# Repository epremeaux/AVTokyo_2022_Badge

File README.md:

## AVTokyo 2022 event badge

### MQTT enabled, Hacker tools, Sensors and Games on ESP32
The AVTokyo 2022 event attendee badge was designed and produced by VPCAsia. Our vision was to provide a useful tool for the attendee not only at the event, but far into the future.

It is based on an 8MB ESP32 with 280x240 pixel TFT full color display (sourced from smart watches). Additionally, it includes a joystick (4 directions plus “press to select”), two game buttons (B and A), and two sensors (Temperature/Humidity and Accelerometer). Finally, the device is fully battery powered, relying on an 18650 style Li-ion battery with associated protections and USB charging.

The software runs a variety of open source Arduino libraries. In particular, we utilized [tcMenu](https://www.thecoderscorner.com/products/arduino-libraries/tc-menu/) and TFT_eSPI to provide all of our software UI, and Adafruit libraries to manage sensors and MQTT (Message Queue, Telemetry Transport).

While WiFi is connected and MQTT messaging is enabled, the badge will send Temperature, Humidity and Battery Voltage measurements to an MQTT server every 5 seconds (the interval is redefinable). Additionally, when you obtain a new best personal score on any game, the new score will be queued to be sent in the next MQTT post. While gaming, MQTT posting is temporarily disabled, in order to provide the best gaming experience.

Here is a video:

## Tour of the Board
Most of the badge components are self-explanatory, but I will attempt to highlight the main components and features. The circuitry between the joystick and screen is responsible for charging the battery (on the back). This is fed from the USB connector, and will charge the battery even when the badge is switched off. There are two LEDs, Standby and Charge. Once fully charged, the Charge LED will turn off and the Standby LED will light. These are rather bright! I started placing tape over my test units to dampend the brightness. ;)

Directly below the screen are the two sensors. On the right, we have an SHTC3 temperature and humidity sensor. On the left we have the KXTJ3-1057 accelerometer. Its not a particularly expensive device, so don't expect much. It's good enough for basic movement and orientation measurement. In the future, I hope to write some better drivers and filters for it to make the data more usable. At which point, I'll try to make a game using tilt/movement.

Above the power switch (bottom right) we have the battery protection circuits and voltage regulator which powers the board. The protection circuit is a very basic back to back mosfet configuration. The control IC *Should* cut power when the battery voltage gets below 3.2, but in my testing this turned out not to be the case. So, until I perform further tests, please dont trust this circuit to protect your battery from long term discharge. Remove the battery for storage.

Speaking of that power switch....   :(     Yes, now we know it's terrible. Attendee @mimura1133 found some alternate part numbers from Digikey if you have the skills to replace the switch. EG1215AA and CUS-12TB should fit. The part used on the badge is from G-Switch, MK-12C02-GXXX. We have yet to determine if this was a case of bad quality switches, or something in the reflow oven process made some of the switch plastics brittle. While this issue seemed considerable at the time of the event, we only had 42 total switch failures (of 400). The cracked resistor on the joystick was actually a higher failure rate.

Above the screen on the left we have the USB connector and associated ESP32 programming circuitry. This consists mainly of a USB to UART interface chip (CH340) and the Enable / Boot config buttons. Under normal circumstances using USB to program the badge, you should not need to bother with the buttons. If you get into a jam though, its nice to be able to manually trigger them. Additionally, the left button (enable) can be used as a reset button, so you dont have to toggle the power switch.
The USB connector can not only be used for programming but provides serial output from the ESP32 as well. There are some diagnostic messages as the badge goes through various tasks. The WiFi and Bluetooth scanners also output a lot of additional data here which cant possibly fit on the screen.

At the screen's top right corner we have a user LED and backlight control circuitry. The LED can be used for your own applications as well. We only use it to indicate the completion of the boot process (sort of a debugging tool for us).

Above the right side of the screen on the edge of the PCB we included some features for your own projects and future expansion. First, there is an I2C "Quiic" footprint. You will need to obtain and solder this yourself (was impossible at the time of production due to supply chain issues). This is a JST BM04B-SRSS connector or equivalent. 
To the right of the Quiic connector is a 5 pin header (2.54 mm pitch). This has ground, 3.3 volts, and three free GPIO from the ESP32. We are excited to see what you all come up with for these connections.

The back of the badge is dominated by the large 18650 lithium-ion battery holder at the bottom. Right in the middle is the ribbon cable for the screen. At top center we have the ESP32 module itself. This is an ESP32-Wroom-32 8MB part. Yes, it really IS 8MB. The firmware as flashed on the day of the event has a 4MB partition configuration. However, if you build fresh from this repository, it will build an 8Mb partition. All of our code now occupies only 20%! Lots of room left for more games, tools and custom apps. In the near future we will make some tutorials on how to add your project to the badge menu.

## Fixes to the production version
The PCB production and most of the component mounting was completed by JLCPCB. However, we still had some work to do. We glued the displays to the PCB and soldering the ribbon cable to the backside ourselves. Additionally, we mounted the battery case. However, you may notice some.. urr.. "Corrections" to some parts around the joystick. Unfortunately, I (Emery) made a mistake on the fill pattern, in which two pull-up resistors did not get connected to 3.3 Volts. So, we had to scrape away some of the solder mask and solder zero ohm jumpers to connect these resistors to the 3.3 volt fill. This added a LOT of additional work. The kicad files have been corrected. So if you attempt to produce the board yourself, don't worry.

We did experience a very unusual issue during production. Thankfully, I had created this a hardware test firmware before the final code was complete, so that we could test all functions before performing final firmware flashing. This test code included the Button Test (in the tools menu) as well as the Sensors page to confirm sensors were working.
The issue we found is that many (like, 1 of every 5 to 10) badges would indicate Left on the joystick, permanently. It took some time to identify the issue: The associated pull-up resistor (R8, on the left side of the joystick) was cracked. The crack is nearly impossible to see, even with a good magnifying lense. However, when we attempted to desolder it, it came off in two pieces! We were able to replace this resistor and managed to save 58 badges.

## About the Server
On our server side, we used a variety of services. It all starts by receiving the MQTT message in the MQTT server. From here, messages are written to a database using some custom Java.
From this database we then made web pages to output various statistics. In particular, we wanted to make a scoreboard for the two games included with the badge.

MQTT is simply a message bucket service. Many other services can subscribe to it. In fact, the code which writes to the database simply subscribes to the MQTT messages. Because this concept is so flexible, other services can easily subscribe at the same time.

Node-Red is a very user friendly GUI based data application builder. It was a simple matter to create a Node-Red flow to subscribe to badge topics using wild cards, allowing us to easily gather temperature measurements from ALL badges at once for example. This same flow outputs a web page with gauges, plots and text data. Node-Red performance is not very quick, but because it is only subscribing to topics (and another service handles database work), it has no impact on MQTT or our database.

### WiFi BugHunt
WE had one more game to play at the event: a WiFi BugHunt! These consisted of an ESP32 with battery pack hidden inside the nightclub (see AVTokyo_2022_Badge/Software/AVT_FindMe_Switcher/). Using the WiFi scanner tool in the badge (or your smartphone), players could seek out the three hidden WiFi access points. Once found, there was a QR code printed on the container of the WiFi AP. Scanning the code with your smartphone would bring you to a guest book web page, where you could sign that you found the AP and leave a comment. To make it more challenging, the APs occasionally dropped AP mode and joined local WiFi to send us an MQTT message containing the battery voltage, so we could monitor the devices in real time. It was quite entertaining to see all the script attacks people tried on our guestbook page ;)

## Getting the code up and running
The source code is "almost ready to run". You will need to install an editor such as Visual Studio Code. Within VSCode, add the PlatformIO extension. After opening the sourcecode folder, PlatformIO SHOULD download all the required extensions (mainly the Arduino framework and the ESP32 platform). All the required libraries are already included in the source code folder (.pio/libdeps/esp32dev/).
Depending on your initial VSCode and PlatformIO configuration, you MAY need to add "lorol/LittleFS_esp32@^1.0.6" to the platform.ini file, under the "lib_deps = " heading. If during compile you receive errors concerning LittleFS, either add it to the platform.ini file, or remove it (just add ; to the beginning of the line).

Additionally, you will need to create a "secrets.h" file like so:
```

//wifi
#define SECRET_SSID "your first AP"
#define SECRET_PASS "AP1 password"

#define SECRET_SSID2 "Second AP"
#define SECRET_PASS2 "AP2 password"

#define SECRET_SSID3 "third AP"
#define SECRET_PASS3 "AP3 password"

//mqtt
#define SECRET_SERVER "MQTT URL or IP" 

```

You can add as many WiFi access points as you want. Look at the MyWiFi.cpp file to add them to the array. The badge will first try to connect to whatever AP you have saved manually from the menu system. If that connection fails, it will then scan through the list given at the top of MyWiFi.cpp (the list is filled in from the secrets.h file). It will try to match any of these AP names to a scanned list available. If one matches, it will try to connect.

In addition to WiFi, you may want to point the badge to your own MQTT server. You may enter it manually in the menu, but you may prefer to hard code it. We have only defined the SECRET_SERVER keyword in the secrets.h file. This assumes an unsecured connection. So, you may want to modify MQTT_Sensors.cpp and secrets.h such that you can define a username and access key in secrets.h.

### UPDATE (22/11/24):

While experimenting with some badges, I found that SOME badges have 4MB ESP32 modules, and some have 8MB modules. Of course, we ORDERED 8MB modules. If you are attempting to compile and run this code and the following effects happen (after upload and reset), you likely have a 4MB module:

* red LED at the top right corner of the screen remains dimly light
* nothing displayed on screen
* when using the terminal, you see that the ESP is rapidly rebooting, with the following output: 
```
rst:0x3 (SW_RESET),boot:0x13 (SPI_FAST_FLASH_BOOT)
configsip: 0, SPIWP:0xee
clk_drv:0x00,q_drv:0x00,d_drv:0x00,cs0_drv:0x00,hd_drv:0x00,wp_drv:0x00
mode:DIO, clock div:2
load:0x3fff0030,len:1184
load:0x40078000,len:12776
load:0x40080400,len:3032
entry 0x400805e4
ets Jul 29 2019 12:21:46
```

PlatformIO is building an image set larger than the size of the flash storage area. However, it cannot by itself, verify the size. All the checksums are fine. You can confirm the size of your ESP's flash area yourself though. Look in the upload task terminal. When you hit the compile button (check mark on the bottom of VSCode window), one of hte first few lines will read:
HARDWARE: ESP32 240MHz, 320KB RAM, 4MB Flash
OR
HARDWARE: ESP32 240MHz, 320KB RAM, 8MB Flash

IF you were unlucky enough to get a 4MB module, we are so sorry.. but we cant control unscrupulous suppliers *(
What to do:
in the platformio.ini file, find the line which reads:

```
board_build.partitions = AVT_8MB_huge.csv
```

Change it to read:

```
board_build.partitions = huge_app.csv
```

This will use a standard partition table for a 4MB ESP32, where most of the space is devoted to a single app, plus bootloader. The base AVT code will occupy 51.5%, still leaving plenty of space for future enhancements.
By the way, this partition table is the one used in all of the badges on the day of the event. This is why I did not notice that we had a mix of 4MB and 8MB modules. So, I dont know yet what the statistics are on how many of you have each type.

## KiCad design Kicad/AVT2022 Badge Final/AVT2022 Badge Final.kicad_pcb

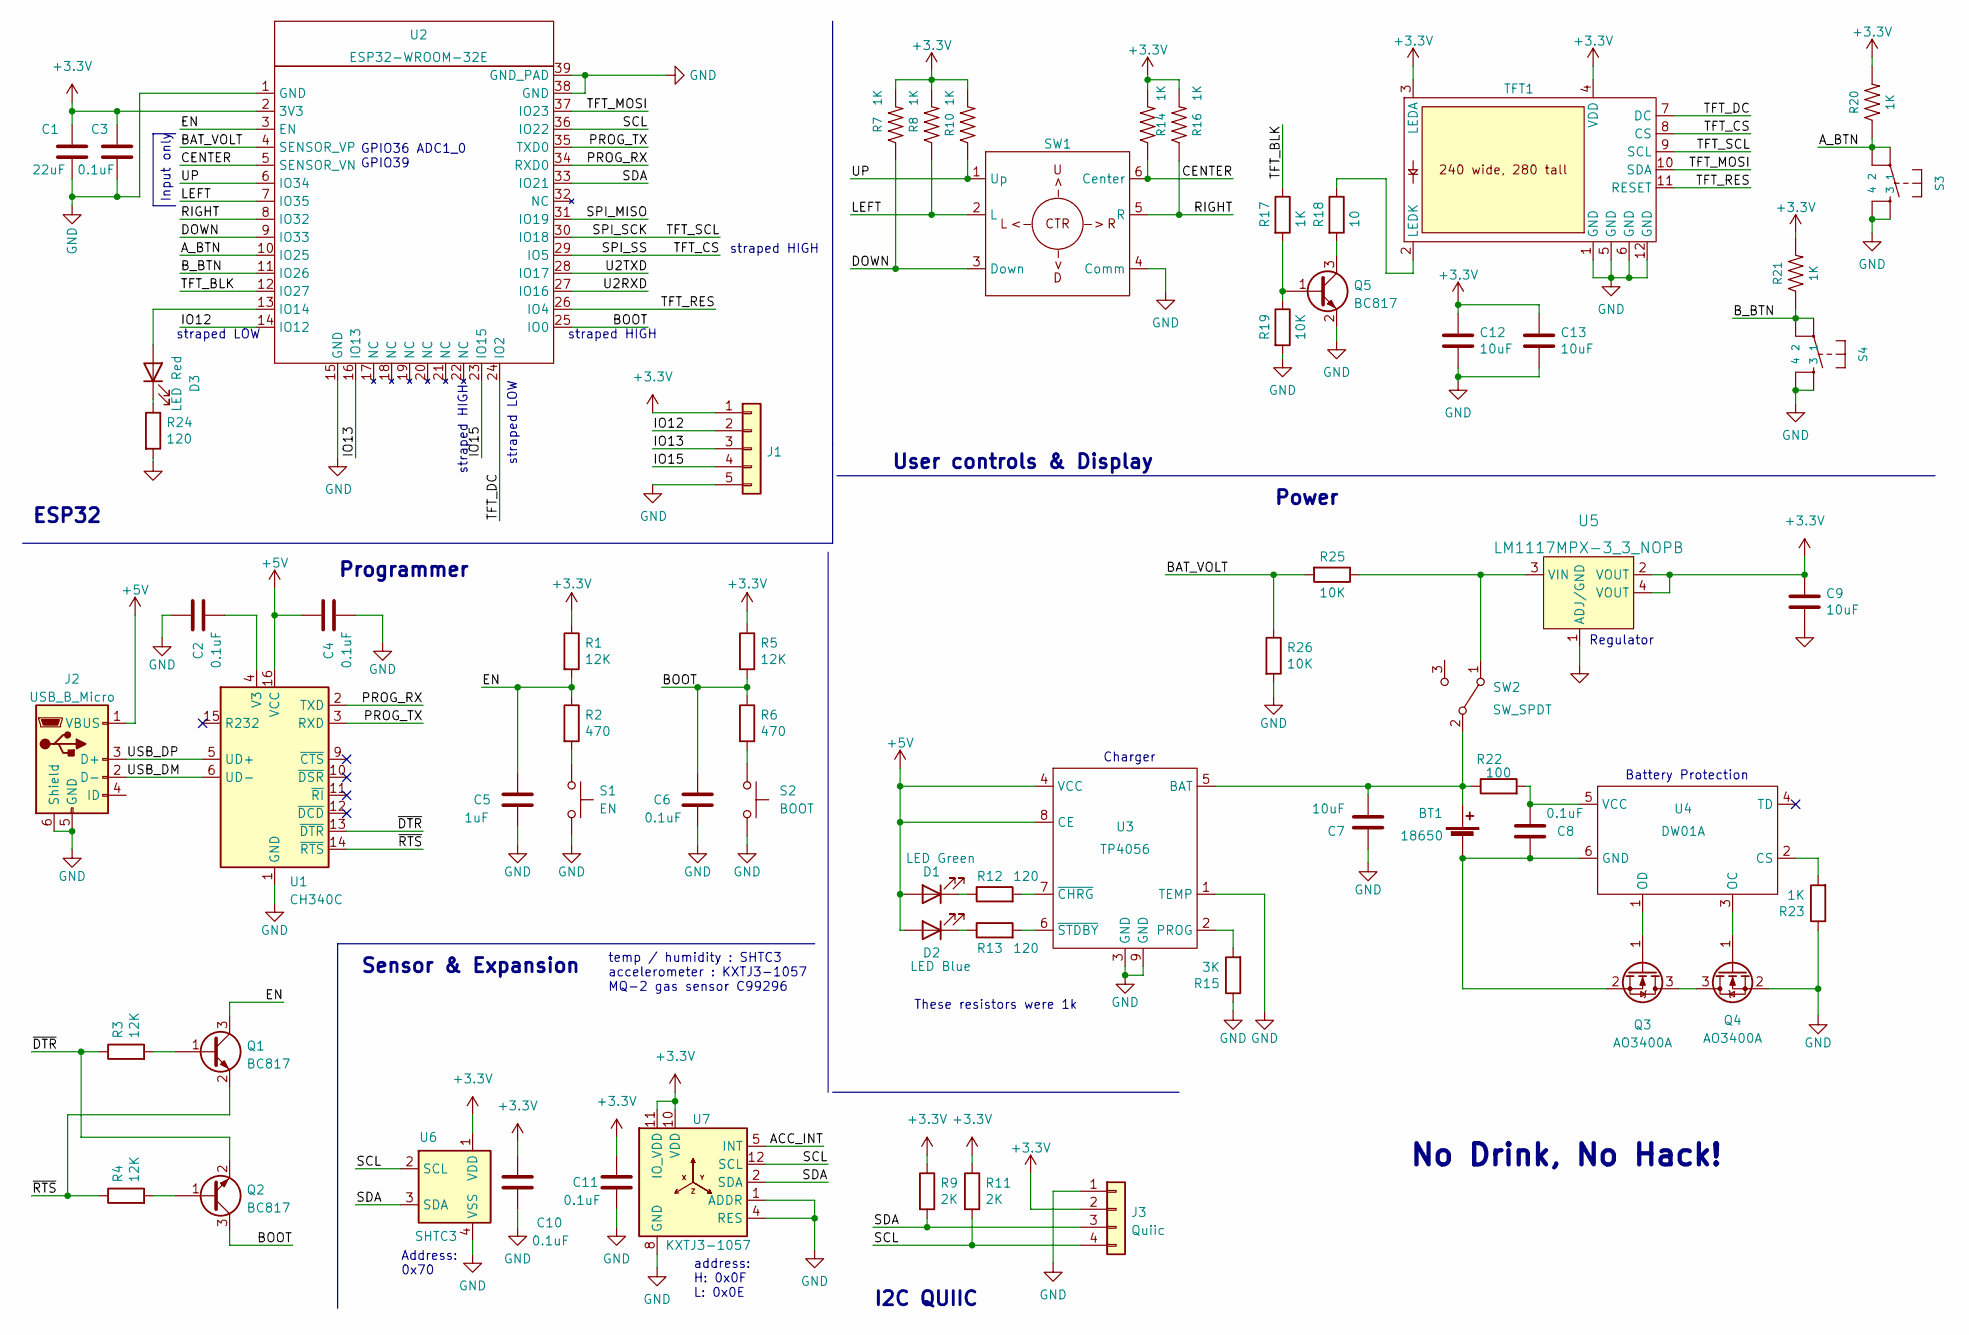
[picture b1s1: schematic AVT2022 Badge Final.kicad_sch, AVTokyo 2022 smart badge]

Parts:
BT1: 18650; BatteryHolder_Keystone_1042_1x18650; JLCPCB Status DO NOT POPULATE
C1: 22uF; C_0805_2012Metric_Pad1.18x1.45mm_HandSolder; JLCPCB# C89572
C2, C3, C4, C6, C8, C10, C11: 0.1uF; C_0805_2012Metric_Pad1.18x1.45mm_HandSolder; JLCPCB# C49678
C5: 1uF; C_0805_2012Metric_Pad1.18x1.45mm_HandSolder; JLCPCB# C28323
C7, C9, C12, C13: 10uF; C_0805_2012Metric_Pad1.18x1.45mm_HandSolder; JLCPCB# C15850
D1: LED Green; LED_0805_2012Metric; JLCPCB Status extended
D2: LED Blue; LED_0805_2012Metric; JLCPCB Status basic
D3: LED Red; LED_0805_2012Metric; JLCPCB Status basic
J1: Conn_01x05; PinHeader_1x05_P2.54mm_Vertical; JLC_Status DO NOT POPULATE
J2: USB_B_Micro; USB_Micro-AB_Molex_47590-0001; JLCPCB Status extended
J3: Quiic; JST_SH_BM04B-SRSS-TB_1x04-1MP_P1.00mm_Vertical; JLC_Status DO NOT POPULATE
Q1, Q2, Q5: BC817; SOT-23; JLCPCB Status extended
Q3, Q4: AO3400A; SOT-23; JLCPCB Status basic
R1, R3, R4, R5: 12K; R_0805_2012Metric_Pad1.20x1.40mm_HandSolder; JLCPCB# C17444
R2, R6: 470; R_0805_2012Metric_Pad1.20x1.40mm_HandSolder; JLCPCB# C17710
R7, R8, R10, R14, R16, R17, R20, R21, R23: 1K; R_0805_2012Metric_Pad1.20x1.40mm_HandSolder; JLCPCB# C17513
R9, R11: 2K; R_0805_2012Metric_Pad1.20x1.40mm_HandSolder; JLCPCB# C17604
R12, R13, R24: 120; R_0805_2012Metric_Pad1.20x1.40mm_HandSolder; JLCPCB# C17437
R15: 3K; R_0805_2012Metric_Pad1.20x1.40mm_HandSolder; JLCPCB# C17661
R18: 10; R_0805_2012Metric_Pad1.20x1.40mm_HandSolder; JLCPCB# C176204
R19, R25: 10K; R_0805_2012Metric_Pad1.20x1.40mm_HandSolder; JLCPCB# C17414
R22: 100; R_0805_2012Metric_Pad1.20x1.40mm_HandSolder; JLCPCB# C17408
R26: 10K; R_0805_2012Metric_Pad1.20x1.40mm_HandSolder; JLCPCB# C17621
S1: EN; SW_Push_1P1T_NO_CK_KMR2; JLCPCB Status extended
S2: BOOT; SW_Push_1P1T_NO_CK_KMR2; JLCPCB Status extended
S3, S4: MOMENTARY-SWITCH-SPST-2-SMD-5.2MM; Switch_Tactile_SMD_6x6mm; JLCPCB Status extended
SW1: navigation_switch_K1-1506SN-01; K1-1506SN-01; JLCPCB Status extended
SW2: SW_SPDT; MK-12C02-Gxxx SPDT SMD switch; JLCPCB Status extended
TFT1: TFT_240x280_raw_LH169I-IG01; TFT_240x280_raw_LH169I-IG01_BackSideMount; JLC_Status DO NOT POPULATE
U1: CH340C; SOIC-16_3.9x9.9mm_P1.27mm; JLCPCB Status extended
U2: ESP32-WROOM-32E; JLCPCB Status extended
U3: TP4056; TI_SO-PowerPAD-8; JLCPCB Status extemded
U4: DW01A; SOT-23-6; JLCPCB Status extemded
U5: LM1117MPX-3_3_NOPB; SOT-223; MPN LM1117MPX-3.3/NOPB; Digi-Key_PN LM1117MPX-3.3/NOPBCT-ND
U6: SHTC3; Sensirion_DFN-4-1EP_2x2mm_P1mm_EP0.7x1.6mm; JLCPCB# C194656
U7: KXTJ3-1057; Kionix_LGA-12_2x2mm_P0.5mm_LayoutBorder2x4y; JLCPCB# C442603

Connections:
+3.3V: C1.1, C3.1, C9.1, C10.1, C11.1, C12.1, C13.1, J1.1, J3.2, R1.1, R5.1, R7.2, R8.2, R9.1, R10.2, R11.1, R14.2, R16.2, R20.2, R21.2, TFT1.3 (LEDA), TFT1.4 (VDD), U2.2 (3V3), U5.2 (VOUT), U5.4 (VOUT), U6.1 (VDD), U7.3 (IO_VDD), U7.7 (VDD), U7.10 (VDD), U7.11 (IO_VDD)
+5V: C4.1, D1.2 (A), D2.2 (A), J2.1 (VBUS), U1.16 (VCC), U3.4 (VCC), U3.8 (CE)
/ACC_INT: U7.5 (INT)
/A_BTN: R20.1, S3.1, S3.2, U2.10 (IO25)
/BAT_VOLT: R25.2, R26.1, U2.4 (SENSOR_VP)
/BOOT: C6.1, Q2.3 (C), R5.2, R6.1, U2.25 (IO0)
/B_BTN: R21.1, S4.1, S4.2, U2.11 (IO26)
/CENTER: R14.1, SW1.6 (Center), U2.5 (SENSOR_VN)
/DOWN: R7.1, SW1.3 (Down), U2.9 (IO33)
/EN: C5.1, Q1.3 (C), R1.2, R2.1, U2.3 (EN)
/IO12: J1.2, U2.14 (IO12)
/IO13: J1.3, U2.16 (IO13)
/IO15: J1.4, U2.23 (IO15)
/LEFT: R8.1, SW1.2 (L), U2.7 (IO35)
/PROG_RX: U1.2 (TXD), U2.34 (RXD0)
/PROG_TX: U1.3 (RXD), U2.35 (TXD0)
/RIGHT: R16.1, SW1.5 (R), U2.8 (IO32)
/SCL: J3.4, R11.2, U2.36 (IO22), U6.2 (SCL), U7.12 (SCL)
/SDA: J3.3, R9.2, U2.33 (IO21), U6.3 (SDA), U7.2 (SDA)
/SPI_MISO: U2.31 (IO19)
/SPI_SCK: TFT1.9 (SCL), U2.30 (IO18)
/SPI_SS: TFT1.8 (CS), U2.29 (IO5)
/TFT_BLK: R17.1, U2.12 (IO27)
/TFT_DC: TFT1.7 (DC), U2.24 (IO2)
/TFT_MOSI: TFT1.10 (SDA), U2.37 (IO23)
/TFT_RES: TFT1.11 (RESET), U2.26 (IO4)
/U2RXD: U2.27 (IO16)
/U2TXD: U2.28 (IO17)
/UP: R10.1, SW1.1 (Up), U2.6 (IO34)
/USB_DM: J2.2 (D-), U1.6 (UD-)
/USB_DP: J2.3 (D+), U1.5 (UD+)
/~DTR: Q2.2 (E), R3.1, U1.13 (~DTR)
/~RTS: Q1.2 (E), R4.1, U1.14 (~RTS)
GND: C1.2, C2.1, C3.2, C4.2, C5.2, C6.2, C7.1, C9.2, C10.2, C11.2, C12.2, C13.2, J1.5, J2.5 (GND), J2.6 (Shield), J3.1, Q4.2 (S), Q5.2 (E), R15.1, R19.2, R23.1, R24.2, R26.2, S1.2, S2.2, S3.3, S3.4, S4.3, S4.4, SW1.4 (Comm), TFT1.1 (GND), TFT1.5 (GND), TFT1.6 (GND), TFT1.12 (GND), U1.1 (GND), U2.1 (GND), U2.15 (GND), U2.38 (GND), U2.39 (GND_PAD), U3.1 (TEMP), U3.3 (GND), U3.9 (GND), U5.1 (ADJ/GND), U6.4 (VSS), U7.1 (ADDR), U7.4 (RES), U7.6 (GND), U7.8 (GND), U7.9 (GND)
unnamed: BT1.1 (+), C7.2, R22.1, SW2.2 (B), U3.5 (BAT)
unnamed: BT1.2 (-), C8.1, Q3.2 (S), U4.6 (GND)
unnamed: C2.2, U1.4 (V3)
unnamed: C8.2, R22.2, U4.5 (VCC)
unnamed: D1.1 (K), R12.1
unnamed: D2.1 (K), R13.1
unnamed: D3.1 (K), R24.1
unnamed: D3.2 (A), U2.13 (IO14)
unnamed: Q1.1 (B), R3.2
unnamed: Q2.1 (B), R4.2
unnamed: Q3.1 (G), U4.1 (OD)
unnamed: Q3.3 (D), Q4.3 (D)
unnamed: Q4.1 (G), U4.3 (OC)
unnamed: Q5.1 (B), R17.2, R19.1
unnamed: Q5.3 (C), R18.2
unnamed: R2.2, S1.1
unnamed: R6.2, S2.1
unnamed: R12.2, U3.7 (~CHRG)
unnamed: R13.2, U3.6 (~STDBY)
unnamed: R15.2, U3.2 (PROG)
unnamed: R18.1, TFT1.2 (LEDK)
unnamed: R23.2, U4.2 (CS)
unnamed: R25.1, SW2.1 (A), U5.3 (VIN)

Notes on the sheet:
straped HIGH
straped LOW
ESP32
Charger
GPIO36 ADC1_0 GPIO39
Regulator
temp / humidity : SHTC3 accelerometer : KXTJ3-1057 MQ-2 gas sensor C99296
Power
Address: 0x70
Input only
Battery Protection
These resistors were 1k
address: H: 0x0F L: 0x0E
Programmer
I2C QUIIC
No Drink, No Hack!
Sensor & Expansion
User controls & Display

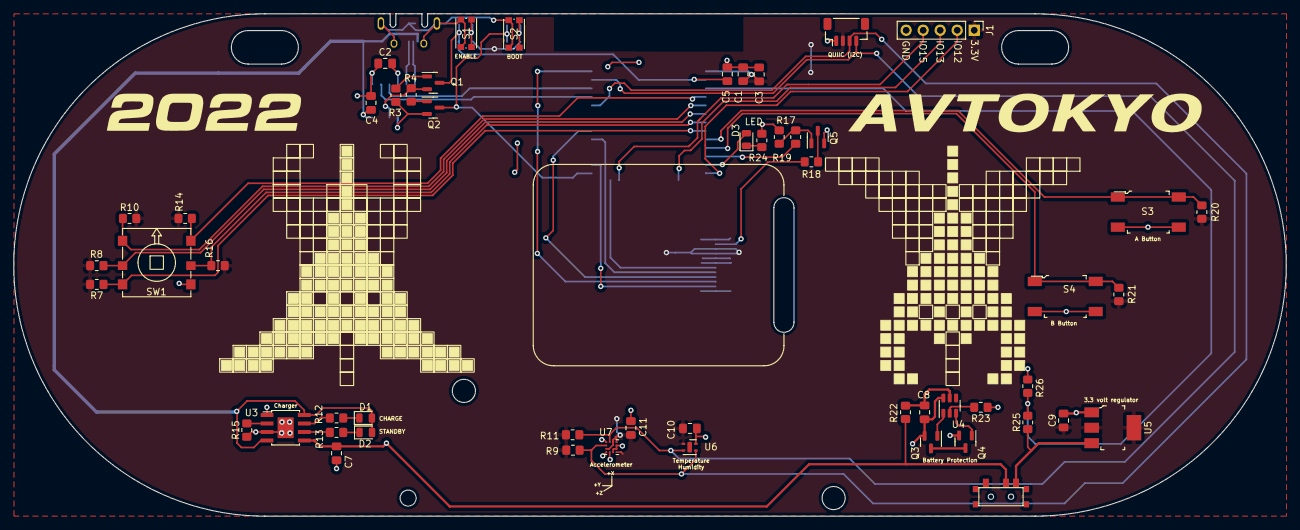
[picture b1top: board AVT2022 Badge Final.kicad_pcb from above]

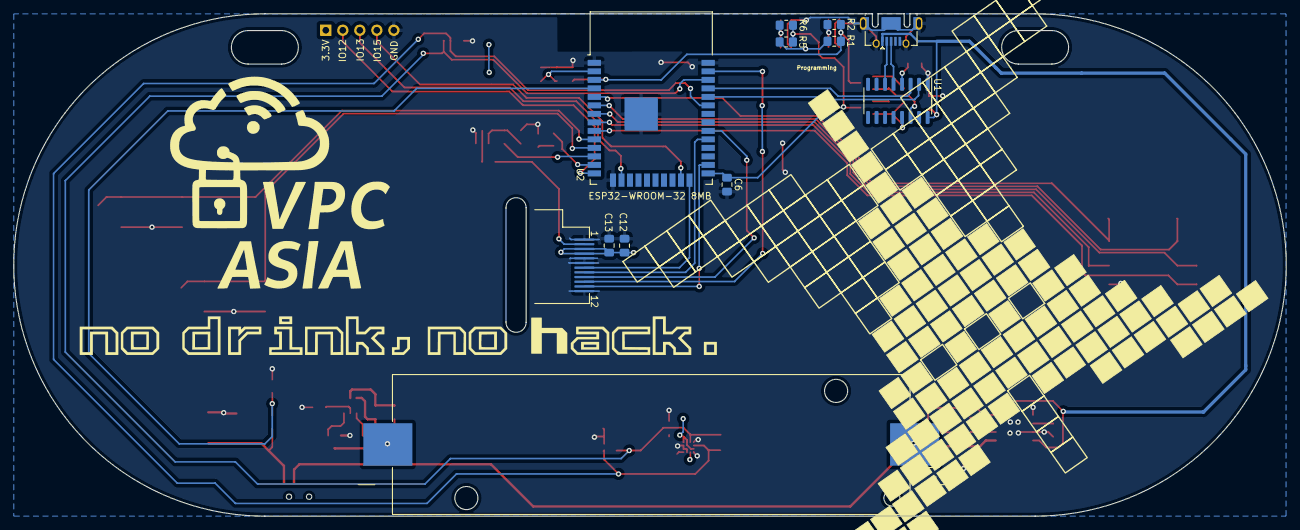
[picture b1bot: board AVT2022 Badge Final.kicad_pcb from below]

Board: 2 copper layers, 190.0 x 75.0 mm, 65 parts (11 on the bottom side), 53 nets.

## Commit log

2022-11-14 more documentation images
2022-11-14 Images
    adding images used to build icons, silk screen, icons, etc. Also promo images for use in the documentation.
2022-11-14 Remove littlefs dep
2022-11-14 Check in mqtt-server.js
    nodejs based simple mqtt server to handle badge messages. Storing message values into various databases.
2022-11-24 Update README.md
    comments regarding 4/8MB modules and how to solve compiler errors on a 4MB module (identify its 4mb, change the partition table in platformio.ini)
